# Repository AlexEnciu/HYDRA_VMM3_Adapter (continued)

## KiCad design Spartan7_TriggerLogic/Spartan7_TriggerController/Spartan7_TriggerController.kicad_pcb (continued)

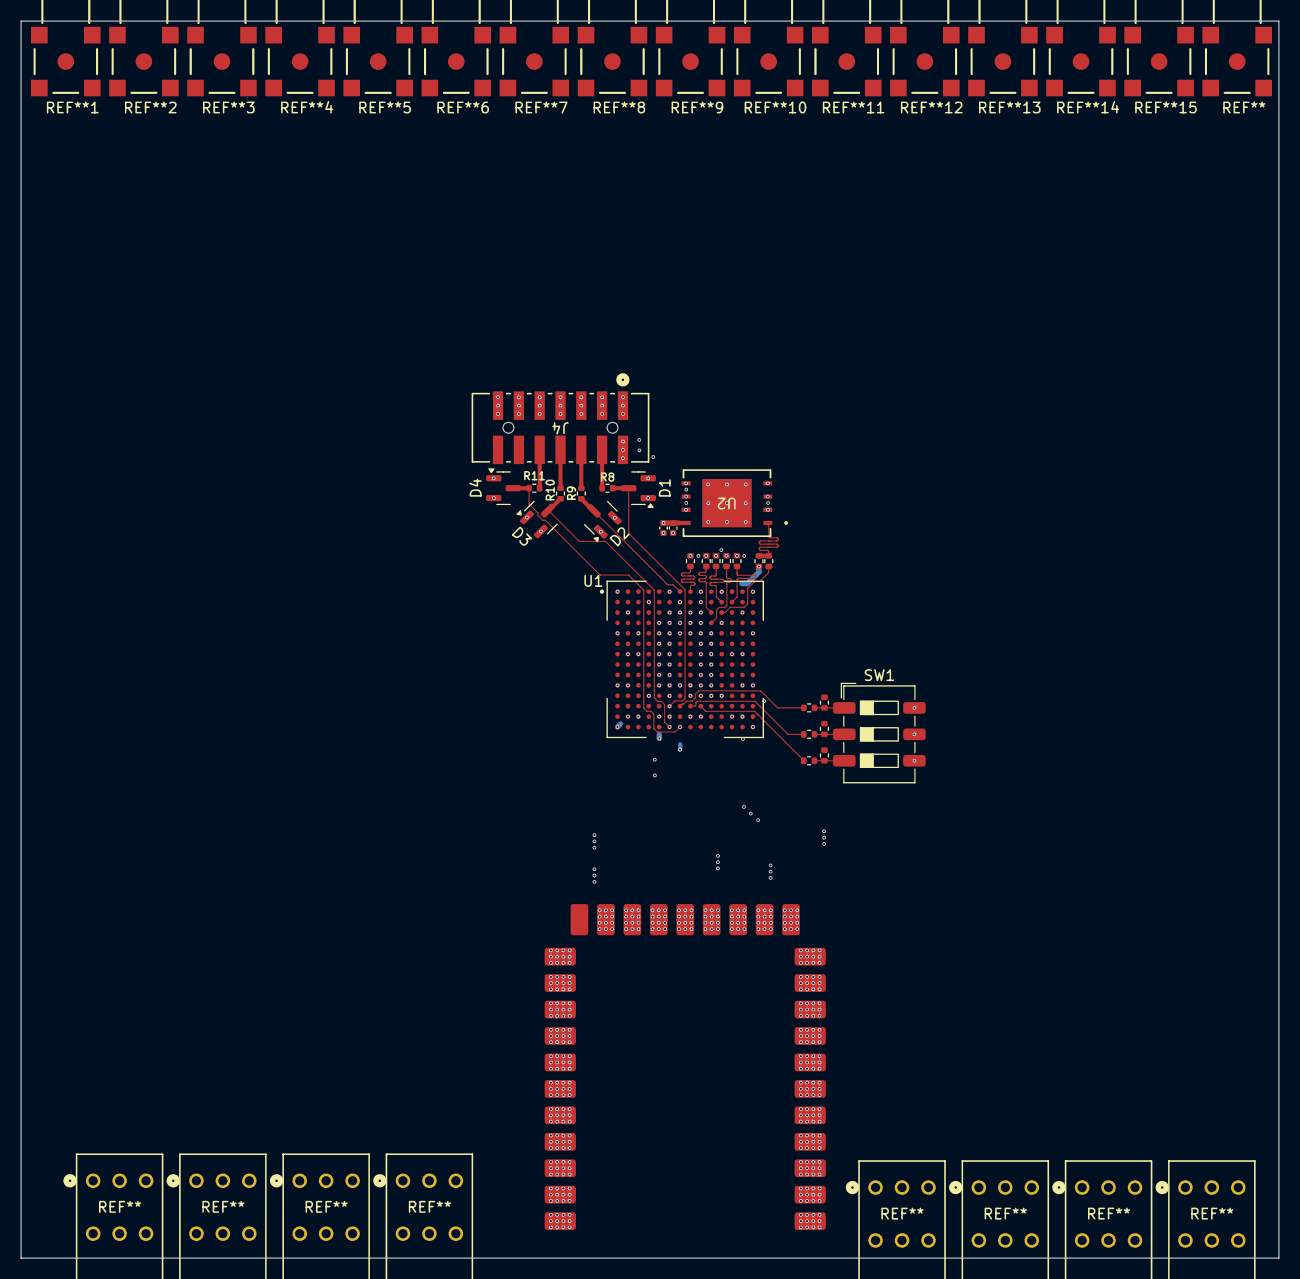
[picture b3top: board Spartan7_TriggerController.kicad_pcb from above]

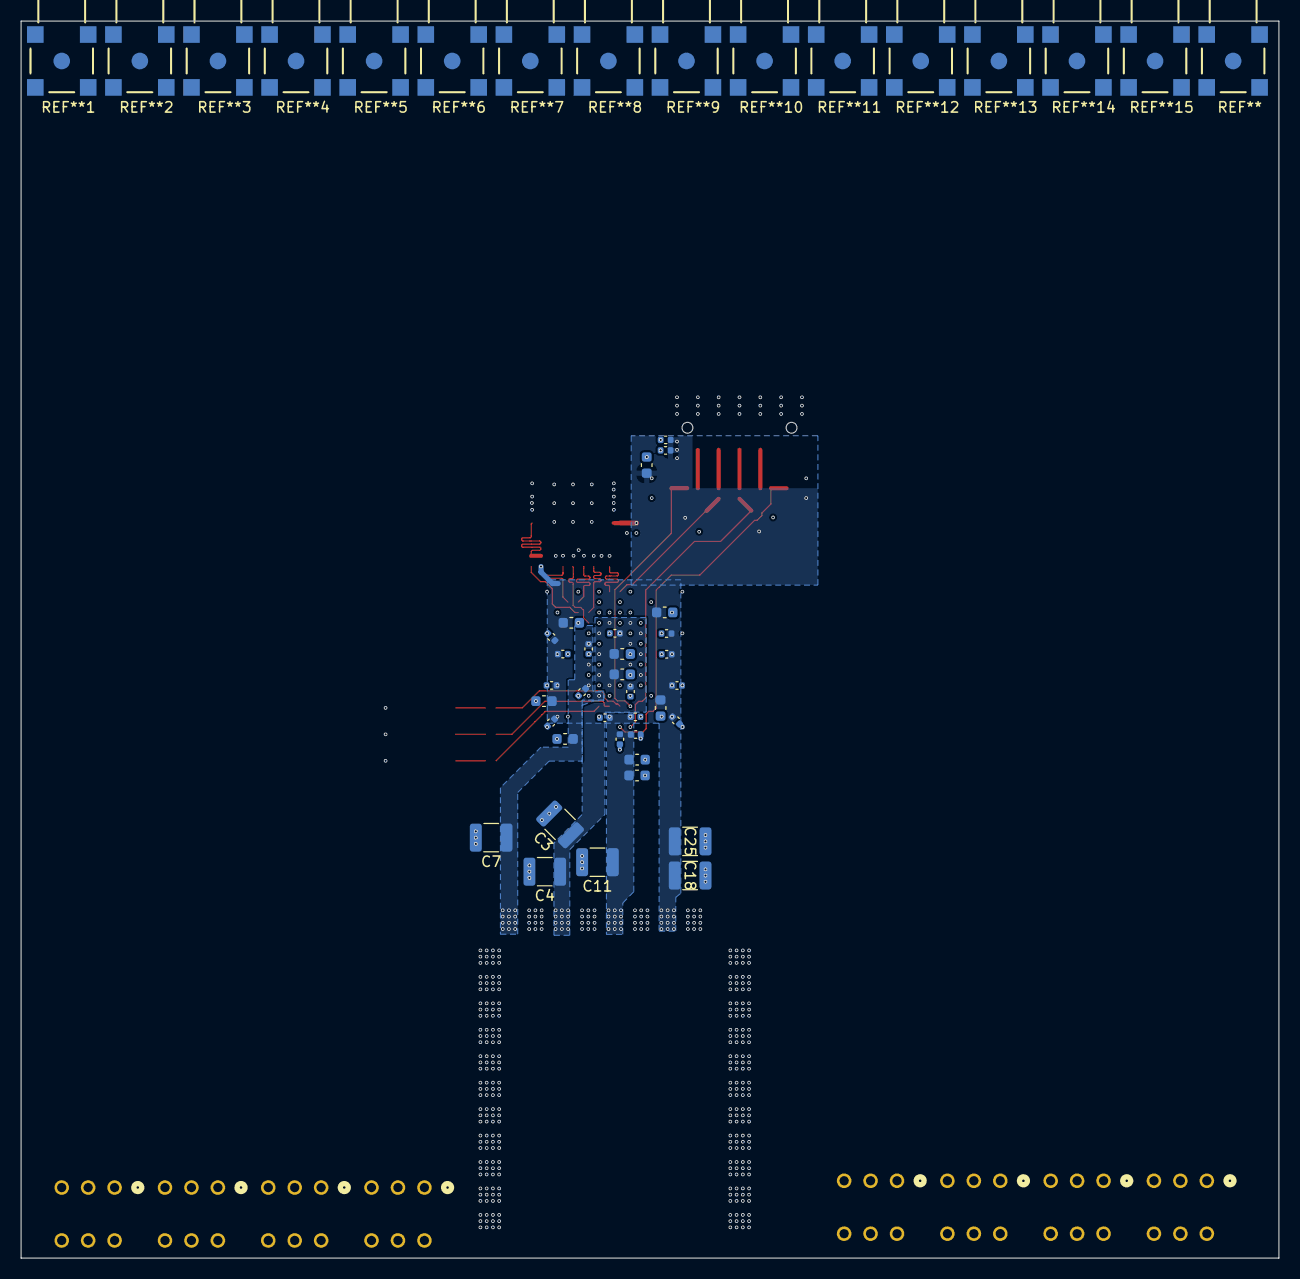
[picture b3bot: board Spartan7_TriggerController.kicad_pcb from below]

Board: 6 copper layers, 120.8 x 118.8 mm, 64 parts (34 on the bottom side), 31 nets.

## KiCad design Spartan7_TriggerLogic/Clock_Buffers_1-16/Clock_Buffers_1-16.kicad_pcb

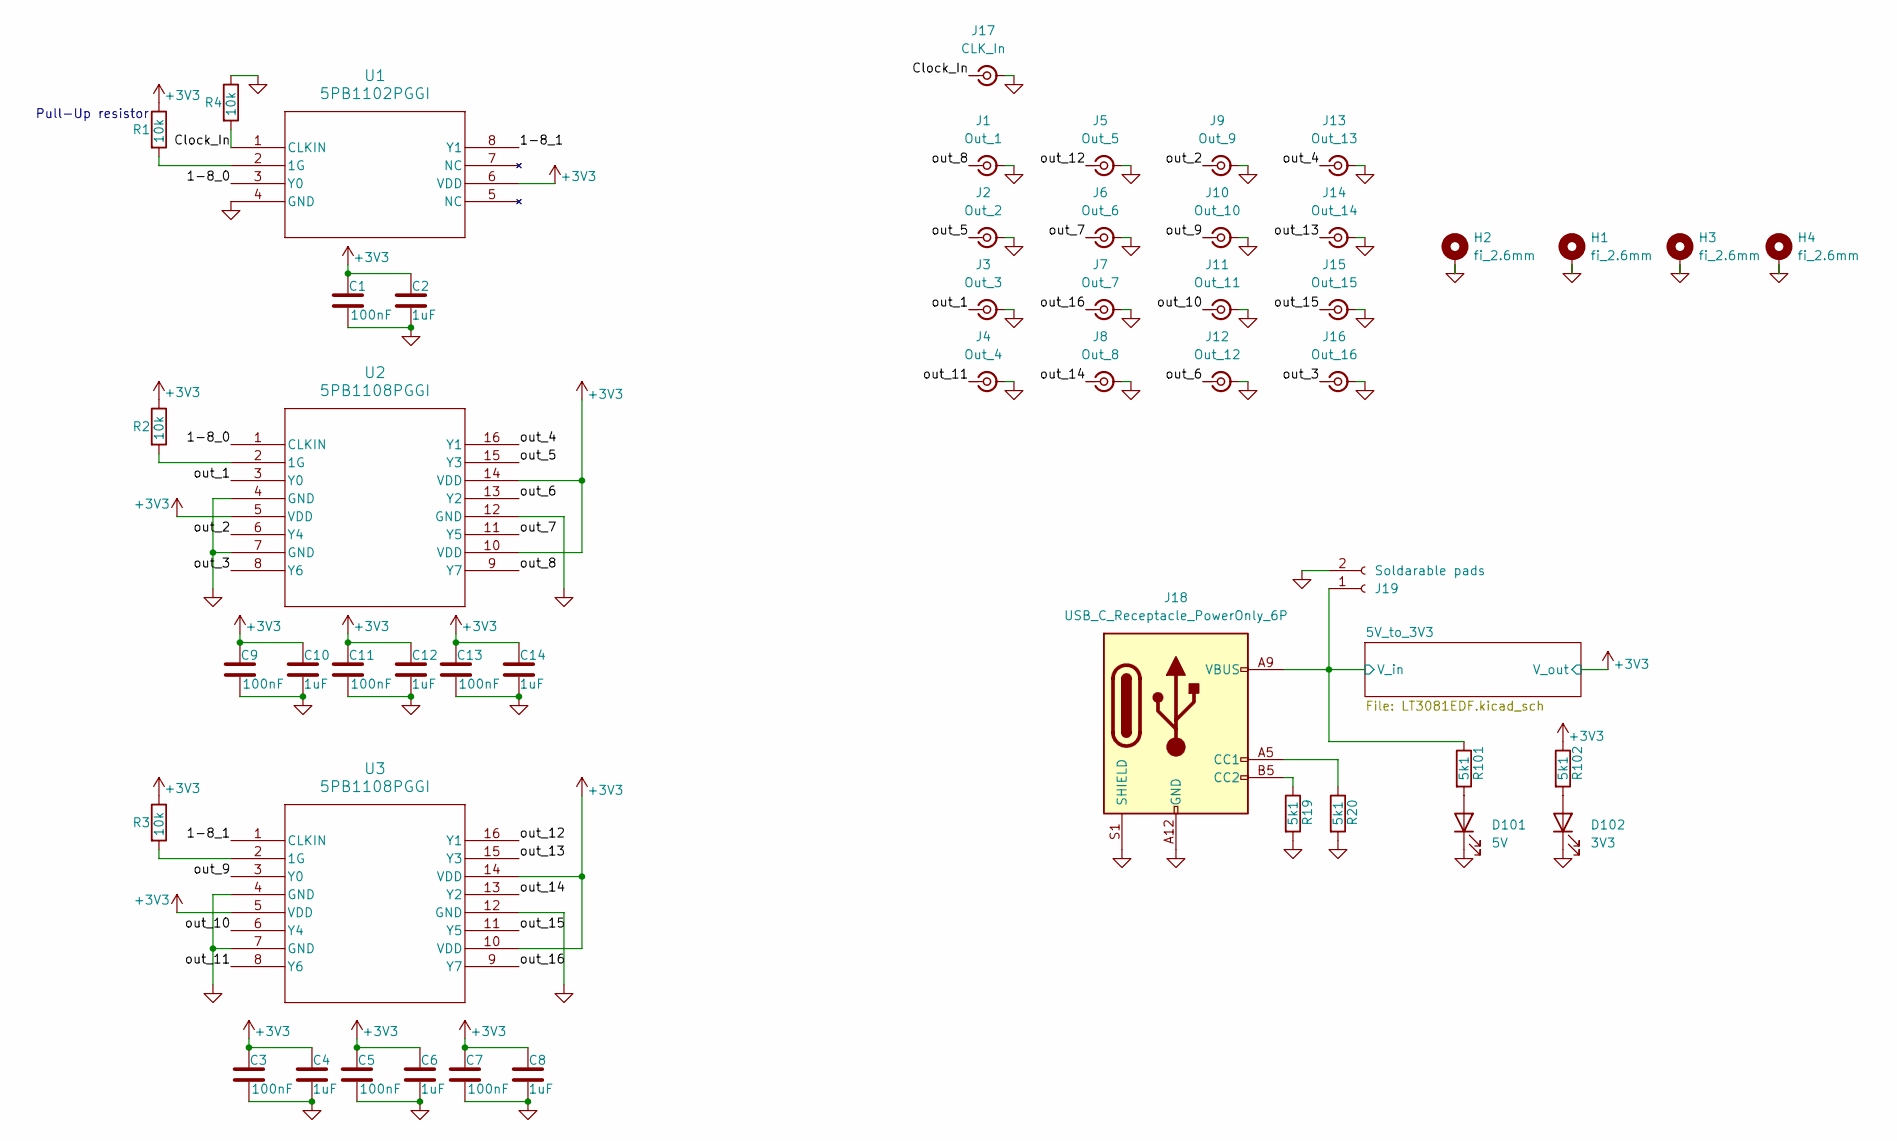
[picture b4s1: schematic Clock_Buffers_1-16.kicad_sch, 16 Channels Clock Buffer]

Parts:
C1, C3, C5, C7, C9, C11, C13: 100nF; C_0402_1005Metric
C2, C4, C6, C8, C10, C12, C14: 1uF; C_0402_1005Metric
D101: 5V; LED_0603_1608Metric
D102: 3V3; LED_0603_1608Metric
H1, H2, H3, H4: fi_2.6mm; MountingHole_2.7mm_M2.5_Pad_Via
J1: Out_1; LINX_CONMCX002-SMD-T
J2: Out_2; LINX_CONMCX002-SMD-T
J3: Out_3; LINX_CONMCX002-SMD-T
J4: Out_4; LINX_CONMCX002-SMD-T
J5: Out_5; LINX_CONMCX002-SMD-T
J6: Out_6; LINX_CONMCX002-SMD-T
J7: Out_7; LINX_CONMCX002-SMD-T
J8: Out_8; LINX_CONMCX002-SMD-T
J9: Out_9; LINX_CONMCX002-SMD-T
J10: Out_10; LINX_CONMCX002-SMD-T
J11: Out_11; LINX_CONMCX002-SMD-T
J12: Out_12; LINX_CONMCX002-SMD-T
J13: Out_13; LINX_CONMCX002-SMD-T
J14: Out_14; LINX_CONMCX002-SMD-T
J15: Out_15; LINX_CONMCX002-SMD-T
J16: Out_16; LINX_CONMCX002-SMD-T
J17: CLK_In; LINX_CONMCX002-SMD-T
J18: USB_C_Receptacle_PowerOnly_6P; CONN6_USB4125_GCT
J19: Soldarable pads; JST_PH_S2B-PH-K_1x02_P2.00mm_Horizontal
R1, R2, R3, R4: 10k; R_0402_1005Metric
R19, R20, R101, R102: 5k1; R_0402_1005Metric
U1: 5PB1102PGGI
U2, U3: 5PB1108PGGI; 5PB1108PGGI_REN

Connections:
+3V3: C1.1, C2.1, C3.1, C4.1, C5.1, C6.1, C7.1, C8.1, C9.1, C10.1, C11.1, C12.1, C13.1, C14.1, R1.1, R2.1, R3.1, R102.1, U1.6 (VDD), U2.5 (VDD), U2.10 (VDD), U2.14 (VDD), U3.5 (VDD), U3.10 (VDD), U3.14 (VDD); also elsewhere on the board
/1-8_0: U1.3 (Y0), U2.1 (CLKIN)
/1-8_1: U1.8 (Y1), U3.1 (CLKIN)
/5V_to_3V3/V_in: J18.A9 (VBUS), J18.B9 (VBUS), J19.1, R101.1; also elsewhere on the board
/Clock_In: J17.1 (In), R4.2, U1.1 (CLKIN)
/out_1: J3.1 (In), U2.3 (Y0)
/out_2: J9.1 (In), U2.6 (Y4)
/out_3: J16.1 (In), U2.8 (Y6)
/out_4: J13.1 (In), U2.16 (Y1)
/out_5: J2.1 (In), U2.15 (Y3)
/out_6: J12.1 (In), U2.13 (Y2)
/out_7: J6.1 (In), U2.11 (Y5)
/out_8: J1.1 (In), U2.9 (Y7)
/out_9: J10.1 (In), U3.3 (Y0)
/out_10: J11.1 (In), U3.6 (Y4)
/out_11: J4.1 (In), U3.8 (Y6)
/out_12: J5.1 (In), U3.16 (Y1)
/out_13: J14.1 (In), U3.15 (Y3)
/out_14: J8.1 (In), U3.13 (Y2)
/out_15: J15.1 (In), U3.11 (Y5)
/out_16: J7.1 (In), U3.9 (Y7)
GND: C1.2, C2.2, C3.2, C4.2, C5.2, C6.2, C7.2, C8.2, C9.2, C10.2, C11.2, C12.2, C13.2, C14.2, D101.1 (K), D102.1 (K), H1.1, H2.1, H3.1, H4.1, J1.2 (Ext), J2.2 (Ext), J3.2 (Ext), J4.2 (Ext), J5.2 (Ext), J6.2 (Ext), J7.2 (Ext), J8.2 (Ext), J9.2 (Ext), J10.2 (Ext), J11.2 (Ext), J12.2 (Ext), J13.2 (Ext), J14.2 (Ext), J15.2 (Ext), J16.2 (Ext), J17.2 (Ext), J18.A12 (GND), J18.B12 (GND), J18.S1 (SHIELD), J19.2, R4.1, R19.2, R20.2, U1.4 (GND), U2.4 (GND), U2.7 (GND), U2.12 (GND), U3.4 (GND), U3.7 (GND), U3.12 (GND); also elsewhere on the board
unnamed: D101.2 (A), R101.2
unnamed: D102.2 (A), R102.2
unnamed: J18.A5 (CC1), R20.1
unnamed: J18.B5 (CC2), R19.1
unnamed: R1.2, U1.2 (1G)
unnamed: R2.2, U2.2 (1G)
unnamed: R3.2, U3.2 (1G)

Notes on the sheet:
Pull-Up resistor

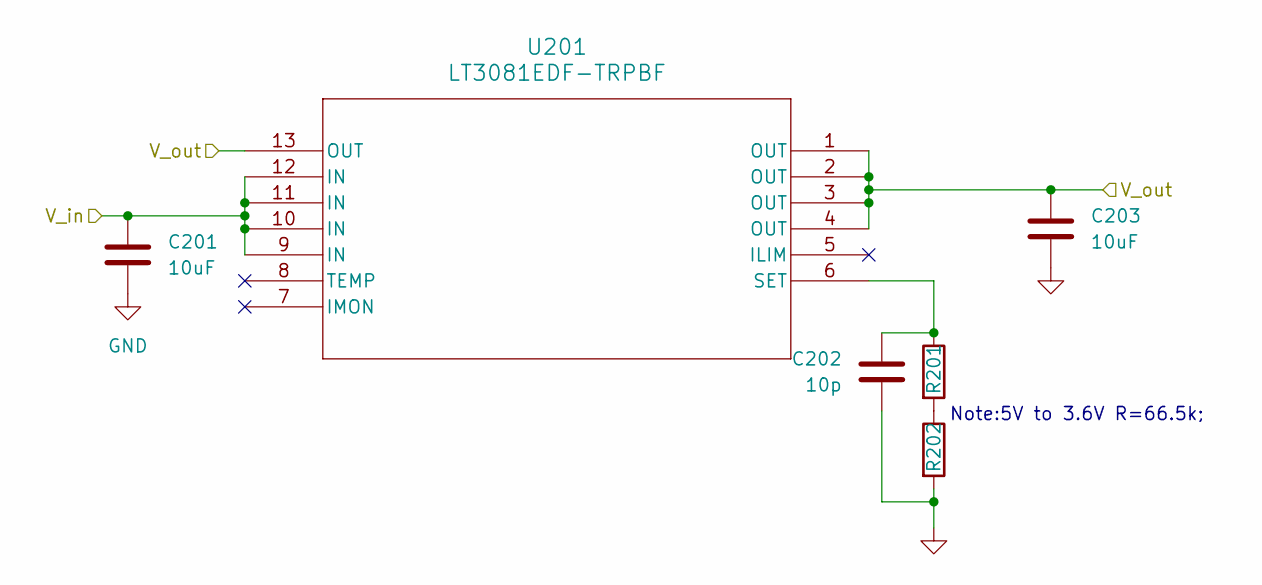
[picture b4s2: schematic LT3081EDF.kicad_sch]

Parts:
C201, C203: 10uF; C_0805_2012Metric
C202: 10p; C_0603_1608Metric
R201, R202: 40k; R_0603_1608Metric
U201: LT3081EDF-TRPBF; DFN-12_DF_LIT

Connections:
+3V3: C203.1, U201.1 (OUT), U201.2 (OUT), U201.3 (OUT), U201.4 (OUT), U201.13 (OUT); also elsewhere on the board
/5V_to_3V3/V_in: C201.1, U201.9 (IN), U201.10 (IN), U201.11 (IN), U201.12 (IN); also elsewhere on the board
GND: C201.2, C202.2, C203.2, R202.2; also elsewhere on the board
unnamed: R201.2, R202.1
unnamed: C202.1, R201.1, U201.6 (SET)

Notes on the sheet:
Note:5V to 3.6V R=66.5k;

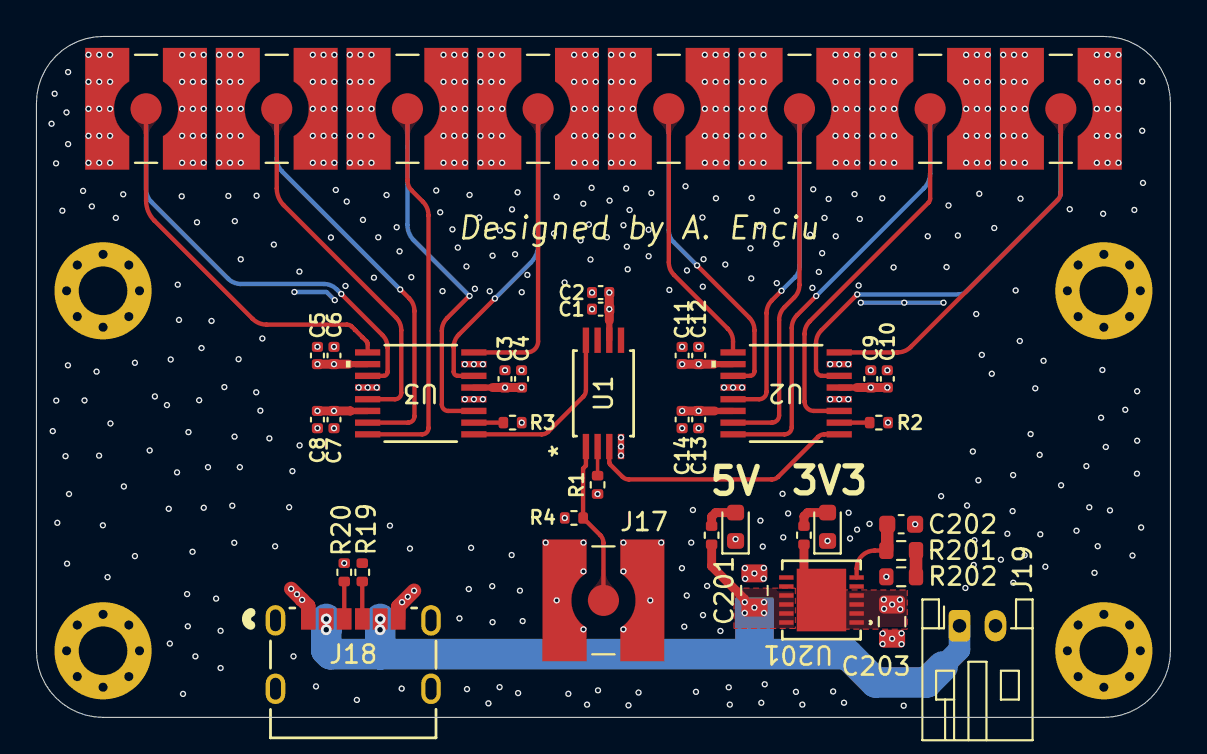
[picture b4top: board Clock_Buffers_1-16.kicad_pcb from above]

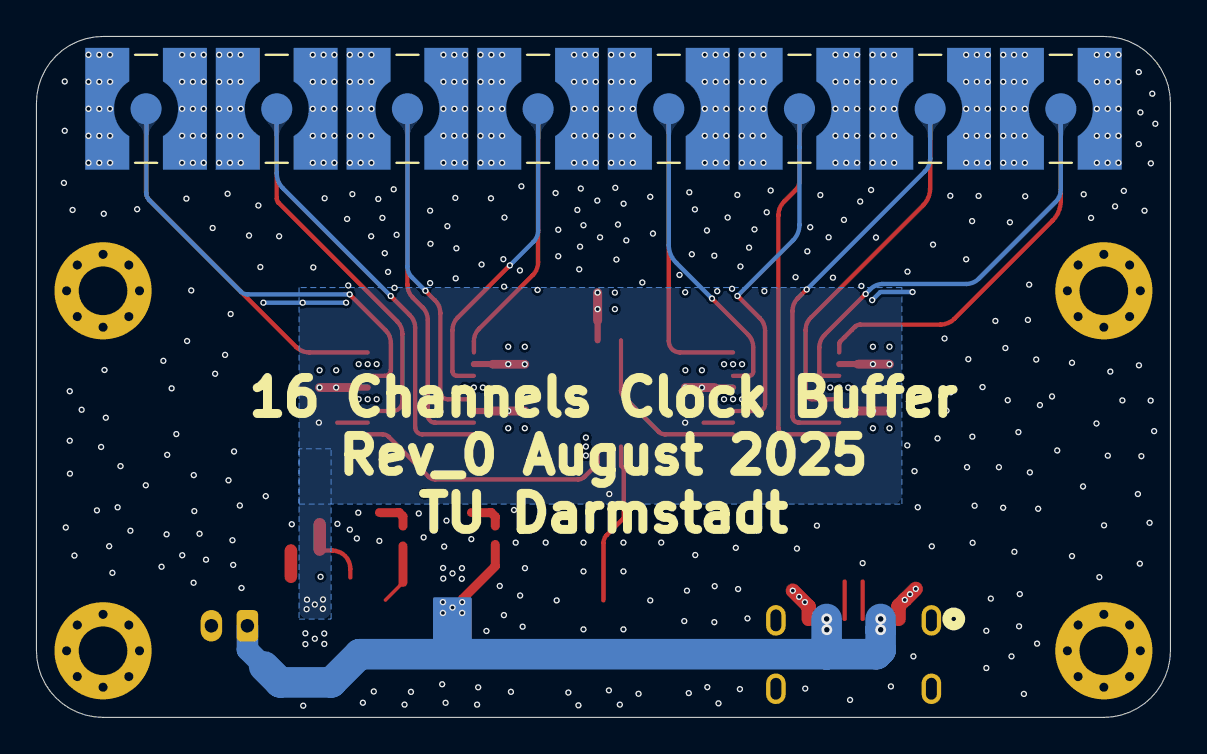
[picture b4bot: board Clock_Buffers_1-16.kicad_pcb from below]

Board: 4 copper layers, 63.0 x 37.8 mm, 56 parts (8 on the bottom side), 31 nets.

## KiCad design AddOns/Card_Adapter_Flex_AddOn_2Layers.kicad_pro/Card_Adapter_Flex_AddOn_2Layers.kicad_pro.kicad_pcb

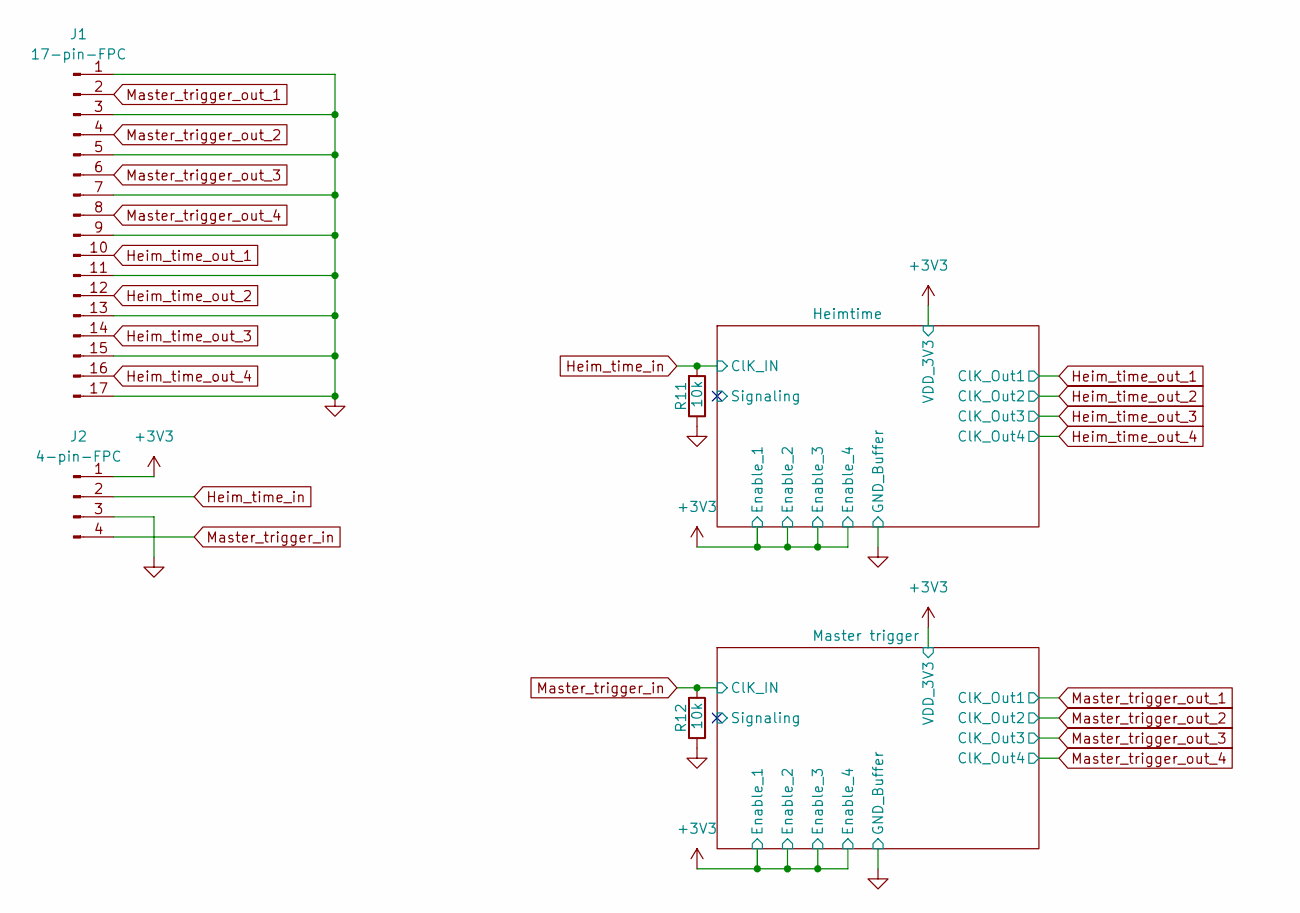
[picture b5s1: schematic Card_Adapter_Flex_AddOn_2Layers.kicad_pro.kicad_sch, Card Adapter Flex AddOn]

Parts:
J1: 17-pin-FPC
J2: 4-pin-FPC
R11, R12: 10k; R_0402_1005Metric

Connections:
+3V3: J2.1; also elsewhere on the board
GND: J1.1, J1.3, J1.5, J1.7, J1.9, J1.11, J1.13, J1.15, J1.17, J2.3, R11.1, R12.1; also elsewhere on the board
Heim_time_in: J2.2, R11.2; also elsewhere on the board
Heim_time_out_1: J1.10; also elsewhere on the board
Heim_time_out_2: J1.12; also elsewhere on the board
Heim_time_out_3: J1.14; also elsewhere on the board
Heim_time_out_4: J1.16; also elsewhere on the board
Master_trigger_in: J2.4, R12.2; also elsewhere on the board
Master_trigger_out_1: J1.2; also elsewhere on the board
Master_trigger_out_2: J1.4; also elsewhere on the board
Master_trigger_out_3: J1.6; also elsewhere on the board
Master_trigger_out_4: J1.8; also elsewhere on the board

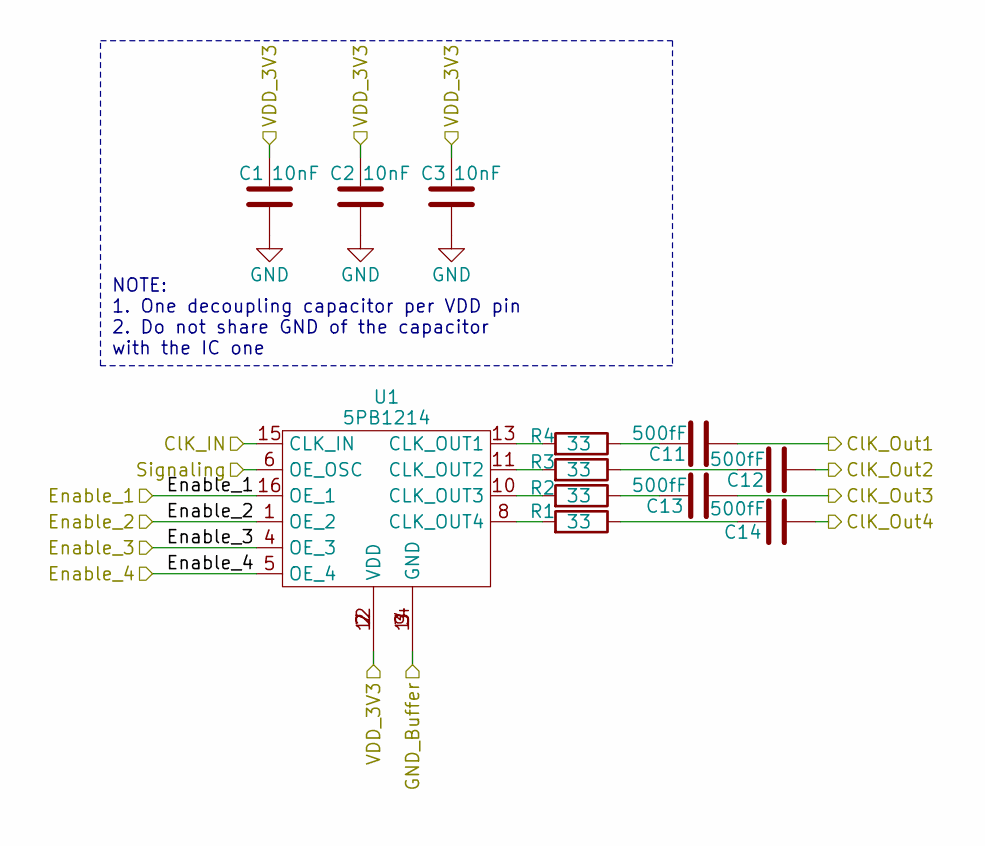
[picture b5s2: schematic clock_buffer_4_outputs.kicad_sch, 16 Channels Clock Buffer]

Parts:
C1, C2, C3: 10nF; C_0402_1005Metric
C11, C12, C13, C14: 500fF; C_0402_1005Metric
R1, R2, R3, R4: 33; R_0402_1005Metric
U1: 5PB1214; 5PB1214CMGK8

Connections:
+3V3: C1.2, C2.2, C3.2, U1.1 (OE_2), U1.2 (VDD), U1.4 (OE_3), U1.5 (OE_4), U1.7 (VDD), U1.12 (VDD), U1.16 (OE_1); also elsewhere on the board
/Heimtime/Signaling: U1.6 (OE_OSC)
GND: C1.1, C2.1, C3.1, U1.3 (GND), U1.9 (GND), U1.14 (GND); also elsewhere on the board
Heim_time_in: U1.15 (CLK_IN); also elsewhere on the board
Heim_time_out_1: C11.1; also elsewhere on the board
Heim_time_out_2: C12.1; also elsewhere on the board
Heim_time_out_3: C13.1; also elsewhere on the board
Heim_time_out_4: C14.1; also elsewhere on the board
unnamed: C11.2, R4.1
unnamed: C12.2, R3.1
unnamed: C13.2, R2.1
unnamed: C14.2, R1.1
unnamed: R4.2, U1.13 (CLK_OUT1)
unnamed: R3.2, U1.11 (CLK_OUT2)
unnamed: R2.2, U1.10 (CLK_OUT3)
unnamed: R1.2, U1.8 (CLK_OUT4)

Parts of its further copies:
C15, C16, C17: 10nF; C_0402_1005Metric
C18, C19, C20, C21: 500fF; C_0402_1005Metric
R13, R14, R15, R16: 33; R_0402_1005Metric
U3: 5PB1214; 5PB1214CMGK8

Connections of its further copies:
+3V3: C15.2, C16.2, C17.2, U3.1 (OE_2), U3.2 (VDD), U3.4 (OE_3), U3.5 (OE_4), U3.7 (VDD), U3.12 (VDD), U3.16 (OE_1); also elsewhere on the board
/Master trigger/Signaling: U3.6 (OE_OSC)
GND: C15.1, C16.1, C17.1, U3.3 (GND), U3.9 (GND), U3.14 (GND); also elsewhere on the board
Master_trigger_in: U3.15 (CLK_IN); also elsewhere on the board
Master_trigger_out_1: C18.1; also elsewhere on the board
Master_trigger_out_2: C19.1; also elsewhere on the board
Master_trigger_out_3: C20.1; also elsewhere on the board
Master_trigger_out_4: C21.1; also elsewhere on the board
unnamed: C18.2, R16.1
unnamed: C19.2, R15.1
unnamed: C20.2, R14.1
unnamed: C21.2, R13.1
unnamed: R16.2, U3.13 (CLK_OUT1)
unnamed: R15.2, U3.11 (CLK_OUT2)
unnamed: R14.2, U3.10 (CLK_OUT3)
unnamed: R13.2, U3.8 (CLK_OUT4)

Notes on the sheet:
NOTE: 1. One decoupling capacitor per VDD pin 2. Do not share GND of the capacitor with the IC one

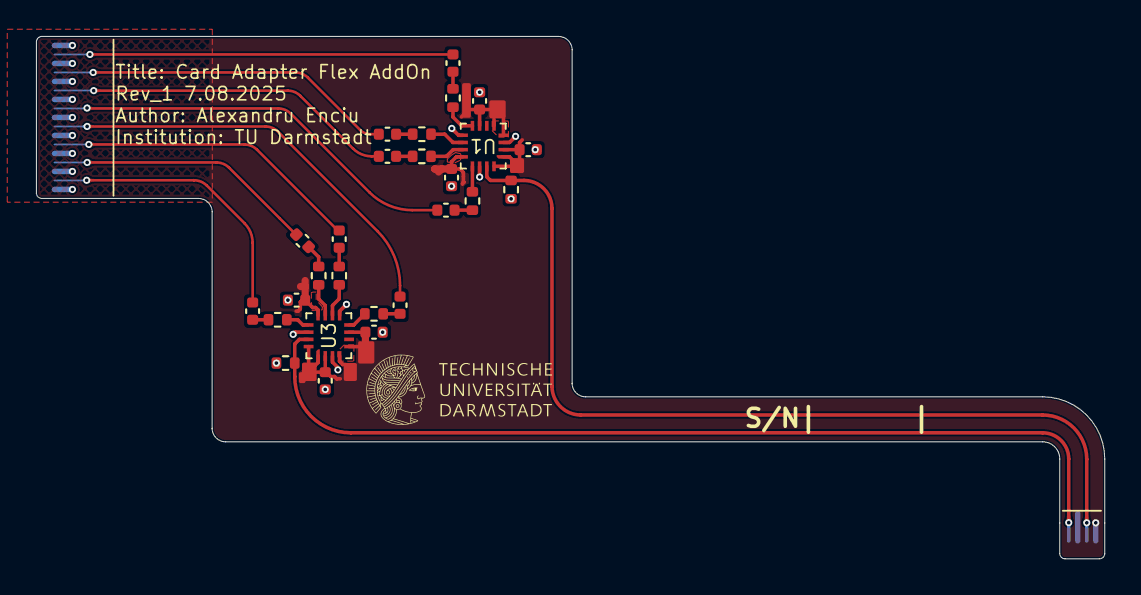
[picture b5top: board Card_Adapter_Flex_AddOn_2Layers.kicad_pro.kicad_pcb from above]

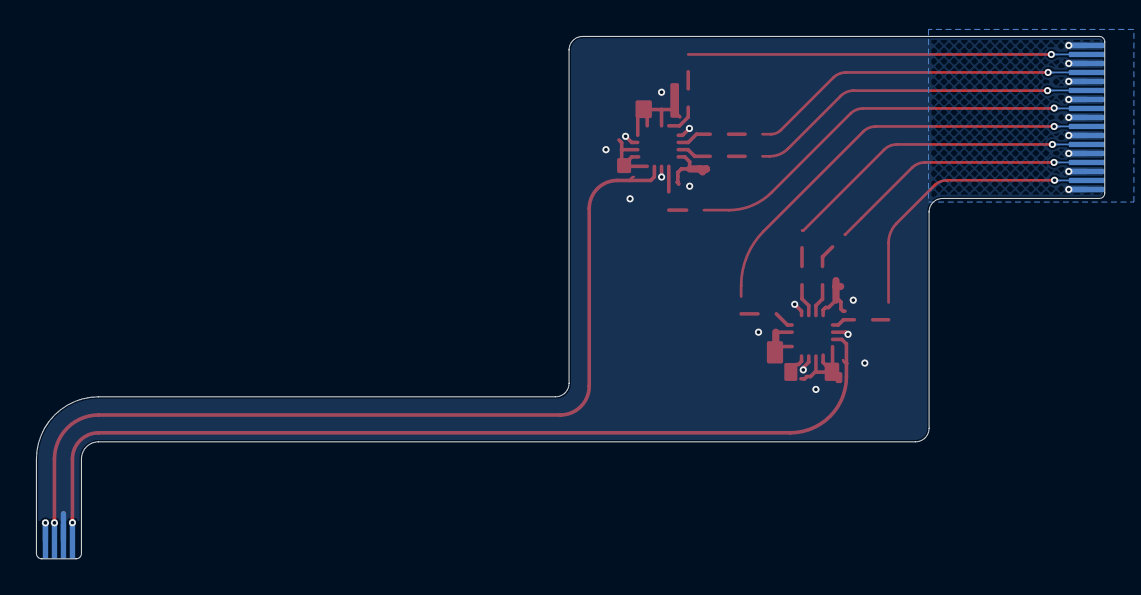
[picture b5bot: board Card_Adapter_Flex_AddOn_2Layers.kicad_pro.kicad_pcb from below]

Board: 2 copper layers, 59.4 x 29.0 mm, 28 parts (2 on the bottom side), 28 nets.

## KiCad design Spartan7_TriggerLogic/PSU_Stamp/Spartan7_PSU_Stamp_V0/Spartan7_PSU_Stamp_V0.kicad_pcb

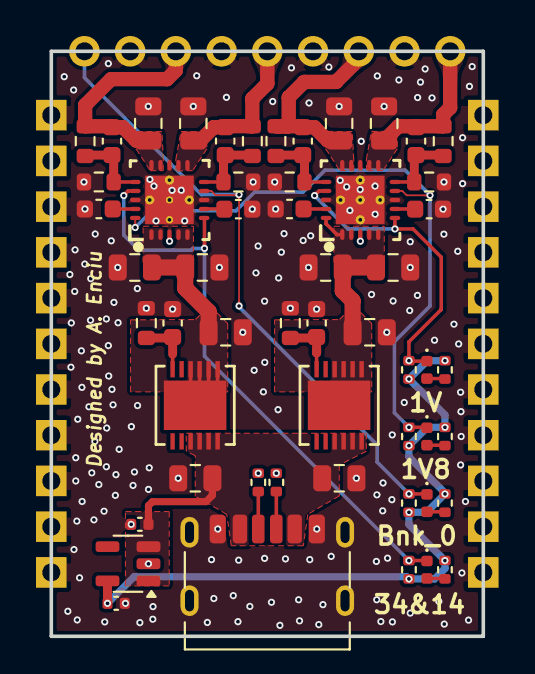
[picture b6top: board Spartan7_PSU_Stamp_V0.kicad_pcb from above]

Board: 4 copper layers, 24.0 x 32.5 mm, 77 parts (0 on the bottom side), 29 nets.

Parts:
C1, C3, C4, C6, C11, C12, C13, C14, C19, C20, C21, C22: 10uF; C_0805_2012Metric
C2, C5: 10p; C_0603_1608Metric
C7, C8, C9, C10: 100nF; C_0603_1608Metric
C15, C16, C17, C18: 10nF; C_0603_1608Metric
C23, C24: 1u; C_0402_1005Metric
D1, D2, D3, D4: 1V_ok; LED_0402_1005Metric
J1: USB4125-GF-A; USB_C_Receptacle_HRO_TYPE-C-31-M-17
J2: Castellated_holes; PinHeader_1x09_P2.54mm_Vertical
J7, J8, J9, J10, J11, J12, J13, J14, J15, J16, J17, J18, J19, J20, J21, J22, J23, J24, J25, J26, J27, J28: Conn_01x01_Pin; PinHeader_1x01_P2.54mm_Vertical
R1, R2: 40k; R_0603_1608Metric
R3, R4: R_3; R_0603_1608Metric
R5, R6: R_4; R_0603_1608Metric
R7, R9: R_1; R_0603_1608Metric
R8, R10: R_2; R_0603_1608Metric
R11, R14, R16, R18: 10k; R_0402_1005Metric
R12, R13, R15, R17: 680; R_0402_1005Metric
R19, R20: 5k1; R_0402_1005Metric
U1, U2: LT3081EDF-TRPBF; DFN-12_DF_LIT-M
U3, U4: TPS7A8801RTJT; RTJ0020D
U5: TPS7A2033; SOT-23-5

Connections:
+3V3: C24.1, R11.1, R12.1, R13.1, R14.1, R15.1, R16.1, R17.1, R18.1, U5.5 (Out)
+5V: C1.1, C4.1, C23.1, J1.A9 (VBUS), J1.B9 (VBUS), U1.9 (IN), U1.10 (IN), U1.11 (IN), U1.12 (IN), U2.9 (IN), U2.10 (IN), U2.11 (IN), U2.12 (IN), U5.1 (In), U5.3 (EN)
/2V5: C3.1, C11.1, C13.1, U1.1 (OUT), U1.2 (OUT), U1.3 (OUT), U1.4 (OUT), U1.13 (OUT), U3.1 (IN1), U3.2 (IN1), U3.4 (IN2), U3.5 (IN2), U3.20 (EN1)
/3V6: C6.1, C12.1, C14.1, U2.1 (OUT), U2.2 (OUT), U2.3 (OUT), U2.4 (OUT), U2.13 (OUT), U4.1 (IN1), U4.2 (IN1), U4.4 (IN2), U4.5 (IN2)
/DONE_0: D4.1 (K), J2.1, R18.2, U4.9 (PG2)
/PG_1V8_ok: D2.1 (K), R14.2, U3.9 (PG2), U4.20 (EN1)
/PG_1V_ok: D1.1 (K), R11.2, U3.6 (EN2), U3.17 (PG1)
/PG_3V3_14_ok: D3.1 (K), R16.2, U4.6 (EN2), U4.17 (PG1)
/V_Bank_14_3V3: C16.1, C22.1, J2.3, R9.1, U4.14 (OUT1), U4.15 (OUT1)
/V_Bank_34_3V3: C18.1, C20.1, J2.5, R4.1, U4.11 (OUT2), U4.12 (OUT2)
/V_aux_1V8: C17.1, C19.1, J2.9, R3.1, U3.11 (OUT2), U3.12 (OUT2)
/V_core_1V: C15.1, C21.1, J2.7, R7.1, U3.14 (OUT1), U3.15 (OUT1)
GND: C1.2, C2.2, C3.2, C4.2, C5.2, C6.2, C7.2, C8.2, C9.2, C10.2, C11.2, C12.2, C13.2, C14.2, C19.2, C20.2, C21.2, C22.2, C23.2, C24.2, J1.A12 (GND), J1.B12 (GND), J1.S1 (SHIELD), J2.2, J2.4, J2.6, J2.8, J7.1, J8.1, J9.1, J10.1, J11.1, J12.1, J13.1, J14.1, J15.1, J16.1, J17.1, J18.1, J19.1, J20.1, J21.1, J22.1, J23.1, J24.1, J25.1, J26.1, J27.1, J28.1, R1.2, R2.2, R5.2, R6.2, R8.2, R10.2, R19.2, R20.2, U3.3 (AGND), U3.8 (SS_CTRL2), U3.13 (AGND), U3.18 (SS_CTRL1), U3.21 (PAD), U4.3 (AGND), U4.8 (SS_CTRL2), U4.13 (AGND), U4.18 (SS_CTRL1), U4.21 (PAD), U5.2 (GND)
unnamed: D1.2 (A), R12.2
unnamed: D2.2 (A), R13.2
unnamed: D3.2 (A), R15.2
unnamed: D4.2 (A), R17.2
unnamed: J1.A5 (CC1), R20.1
unnamed: J1.B5 (CC2), R19.1
unnamed: C2.1, R1.1, U1.6 (SET)
unnamed: C5.1, R2.1, U2.6 (SET)
unnamed: C15.2, R7.2, R8.1, U3.16 (FB1)
unnamed: C17.2, R3.2, R5.1, U3.10 (FB2)
unnamed: C7.1, U3.19 (NR_SS1)
unnamed: C9.1, U3.7 (NR_SS2)
unnamed: C16.2, R9.2, R10.1, U4.16 (FB1)
unnamed: C18.2, R4.2, R6.1, U4.10 (FB2)
unnamed: C8.1, U4.19 (NR_SS1)
unnamed: C10.1, U4.7 (NR_SS2)
